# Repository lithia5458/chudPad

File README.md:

# chudPad Description

The chudPad features a 3x3 macropad as well as a 0.91 inch screen and one knob. Also, it includes the chuds that its named after, debossed onto the front where everyone can marvel in their glory!

# chudPad image

# chudPad schematic

# chudPad PCB

# chudPad case and fit

The screws will insert from the left into the right side, and the heatset inserts will be placed inside of the green top plate.

# BOM

- 9x Cherry MX Switches
- 9x DSA Keycaps
- 4x M3x5x4 Heatset Inserts
- 4x M3x16mm SHCS Bolts
- 9x 1N4148 DO-35 Diodes
- 1x 0.91" 128x32 OLED Display
- 1x XIAO RP2040
- 1x Case (3 printed parts)
- 1x EC11 Rotary Encoder

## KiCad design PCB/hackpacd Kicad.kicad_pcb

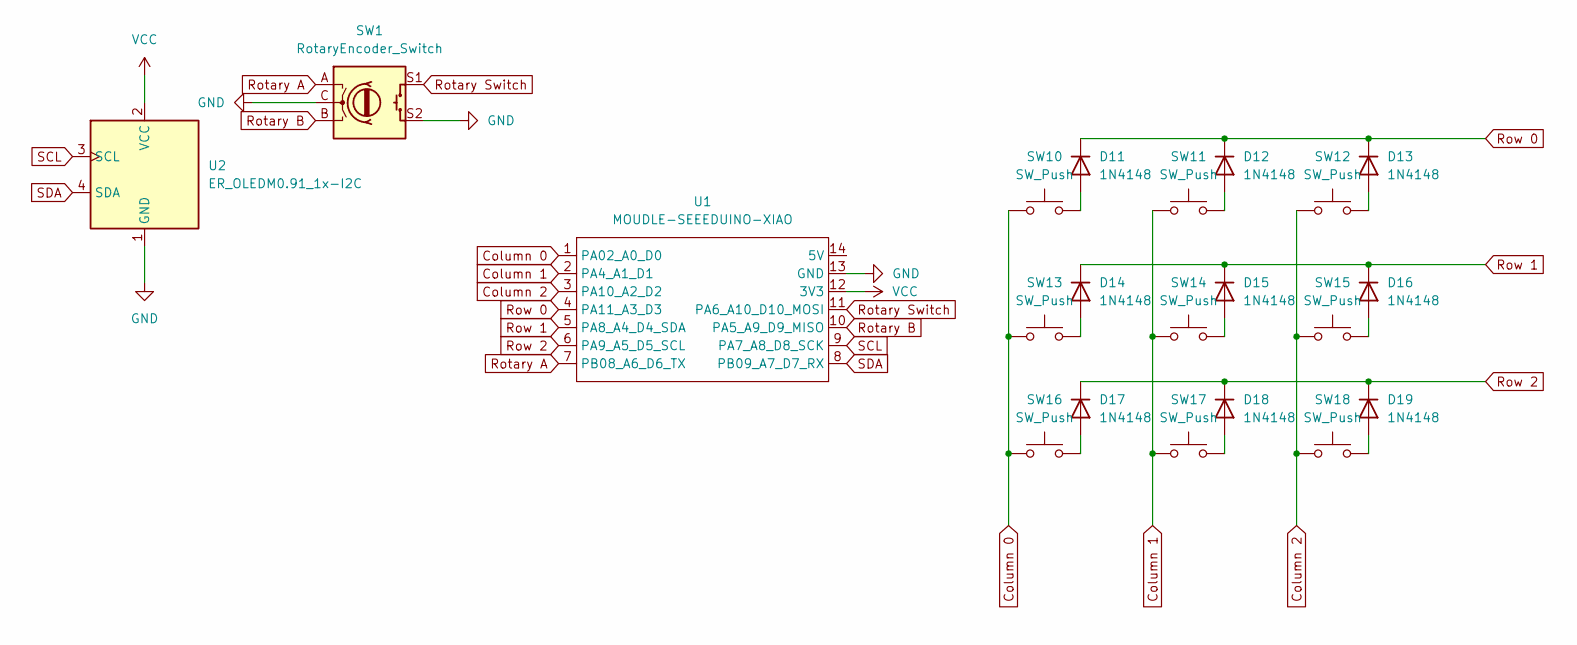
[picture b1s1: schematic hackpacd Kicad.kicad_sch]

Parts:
D11, D12, D13, D14, D15, D16, D17, D18, D19: 1N4148; Diode_DO-35
SW1: RotaryEncoder_Switch; RotaryEncoder_Alps_EC11E-Switch_Vertical_H20mm
SW10, SW11, SW12, SW13, SW14, SW15, SW16, SW17, SW18: SW_Push; MX_PCB_1.00u
U1: MOUDLE-SEEEDUINO-XIAO; XIAO-Generic-Hybrid-14P-2.54-21X17.8MM
U2: ER_OLEDM0.91_1x-I2C

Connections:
Column 0: SW10.1, SW13.1, SW16.1, U1.1 (PA02_A0_D0)
Column 1: SW11.1, SW14.1, SW17.1, U1.2 (PA4_A1_D1)
Column 2: SW12.1, SW15.1, SW18.1, U1.3 (PA10_A2_D2)
GND: SW1.C, SW1.S2, U1.13 (GND), U2.1 (GND)
unnamed: D11.2 (A), SW10.2
unnamed: D12.2 (A), SW11.2
unnamed: D13.2 (A), SW12.2
unnamed: D14.2 (A), SW13.2
unnamed: D15.2 (A), SW14.2
unnamed: D16.2 (A), SW15.2
unnamed: D17.2 (A), SW16.2
unnamed: D18.2 (A), SW17.2
unnamed: D19.2 (A), SW18.2
Rotary A: SW1.A, U1.7 (PB08_A6_D6_TX)
Rotary B: SW1.B, U1.10 (PA5_A9_D9_MISO)
Rotary Switch: SW1.S1, U1.11 (PA6_A10_D10_MOSI)
Row 0: D11.1 (K), D12.1 (K), D13.1 (K), U1.4 (PA11_A3_D3)
Row 1: D14.1 (K), D15.1 (K), D16.1 (K), U1.5 (PA8_A4_D4_SDA)
Row 2: D17.1 (K), D18.1 (K), D19.1 (K), U1.6 (PA9_A5_D5_SCL)
SCL: U1.9 (PA7_A8_D8_SCK), U2.3 (SCL)
SDA: U1.8 (PB09_A7_D7_RX), U2.4 (SDA)
VCC: U1.12 (3V3), U2.2 (VCC)

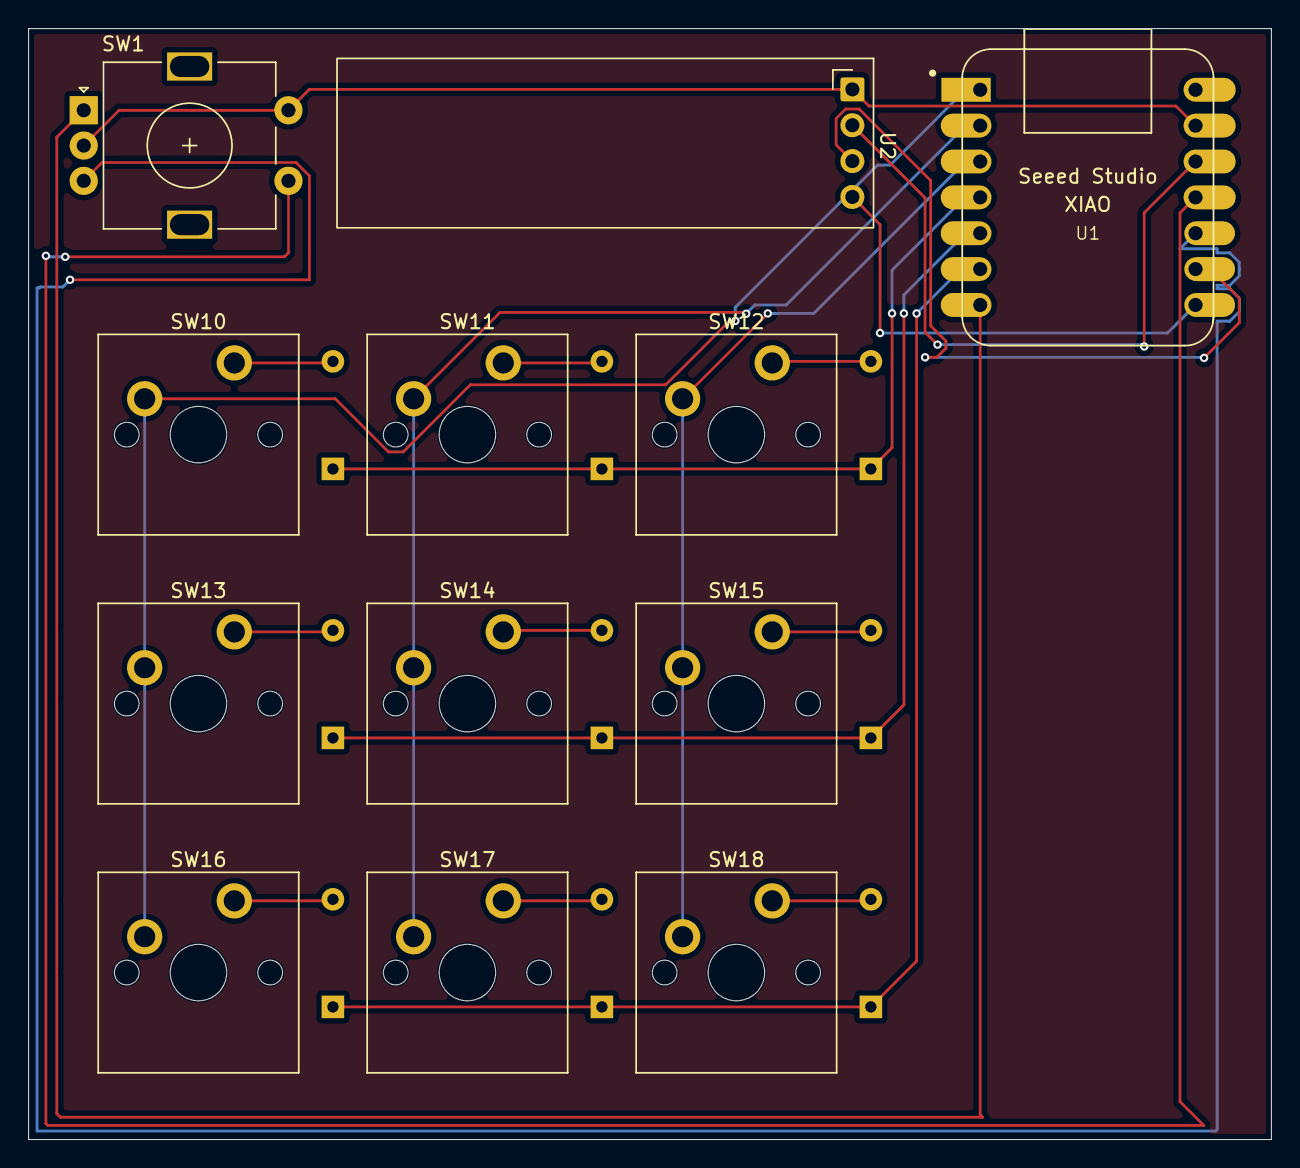
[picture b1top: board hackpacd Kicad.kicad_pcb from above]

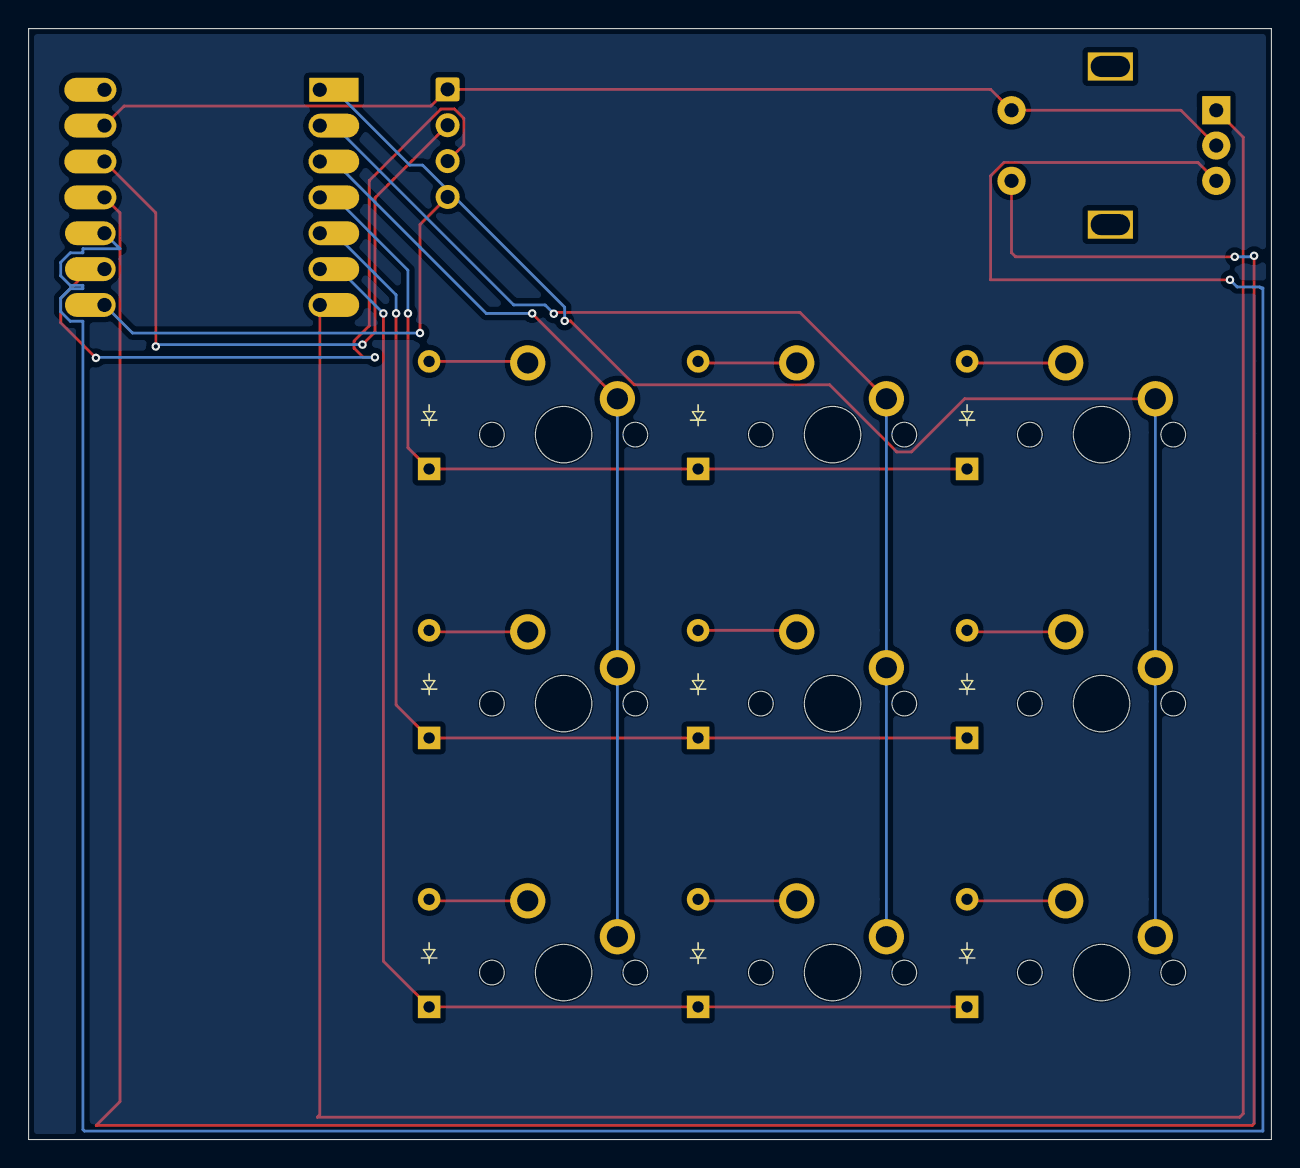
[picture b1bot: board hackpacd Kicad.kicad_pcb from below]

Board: 2 copper layers, 88.0 x 78.7 mm, 21 parts (9 on the bottom side), 22 nets.

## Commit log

2026-06-20 Create CAD
2026-06-20 Create 123
2026-06-20 Add files via upload
    committed initial version
2026-06-20 Create asd
2026-06-20 gitignore
2026-06-21 Expand README.md with chudPad details and images
    Added detailed description, images, schematic, PCB, case fit information, and BOM for chudPad.
